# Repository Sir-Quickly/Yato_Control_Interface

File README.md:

# Yato_Control_Interface
Interface Leiterplatte zur Fernsteuerung von  YATO (YG-04700)- und Hendi (3500 M)-Induktionsplatten 

Achtung: Im Betrieb und selbst im ausgeschalteten Zustand können auf der Leiterplatte potentiell gefährliche Spannungen anliegen, selbst nach dem Ziehen des Netzsteckers durch geladenen Kapzitäten.
Die Benutzung dieses Designs erfolgt auf eigenes Risiko und nur durch fachkundige Personen, die sich über die Gefahren und Risiken im Klaren sind.

Änderungen gegenüber V1.0
- Pulldown Widerstand für das On-Signal von der YATO Poti-Platine
- Pos. R4 korrigiert

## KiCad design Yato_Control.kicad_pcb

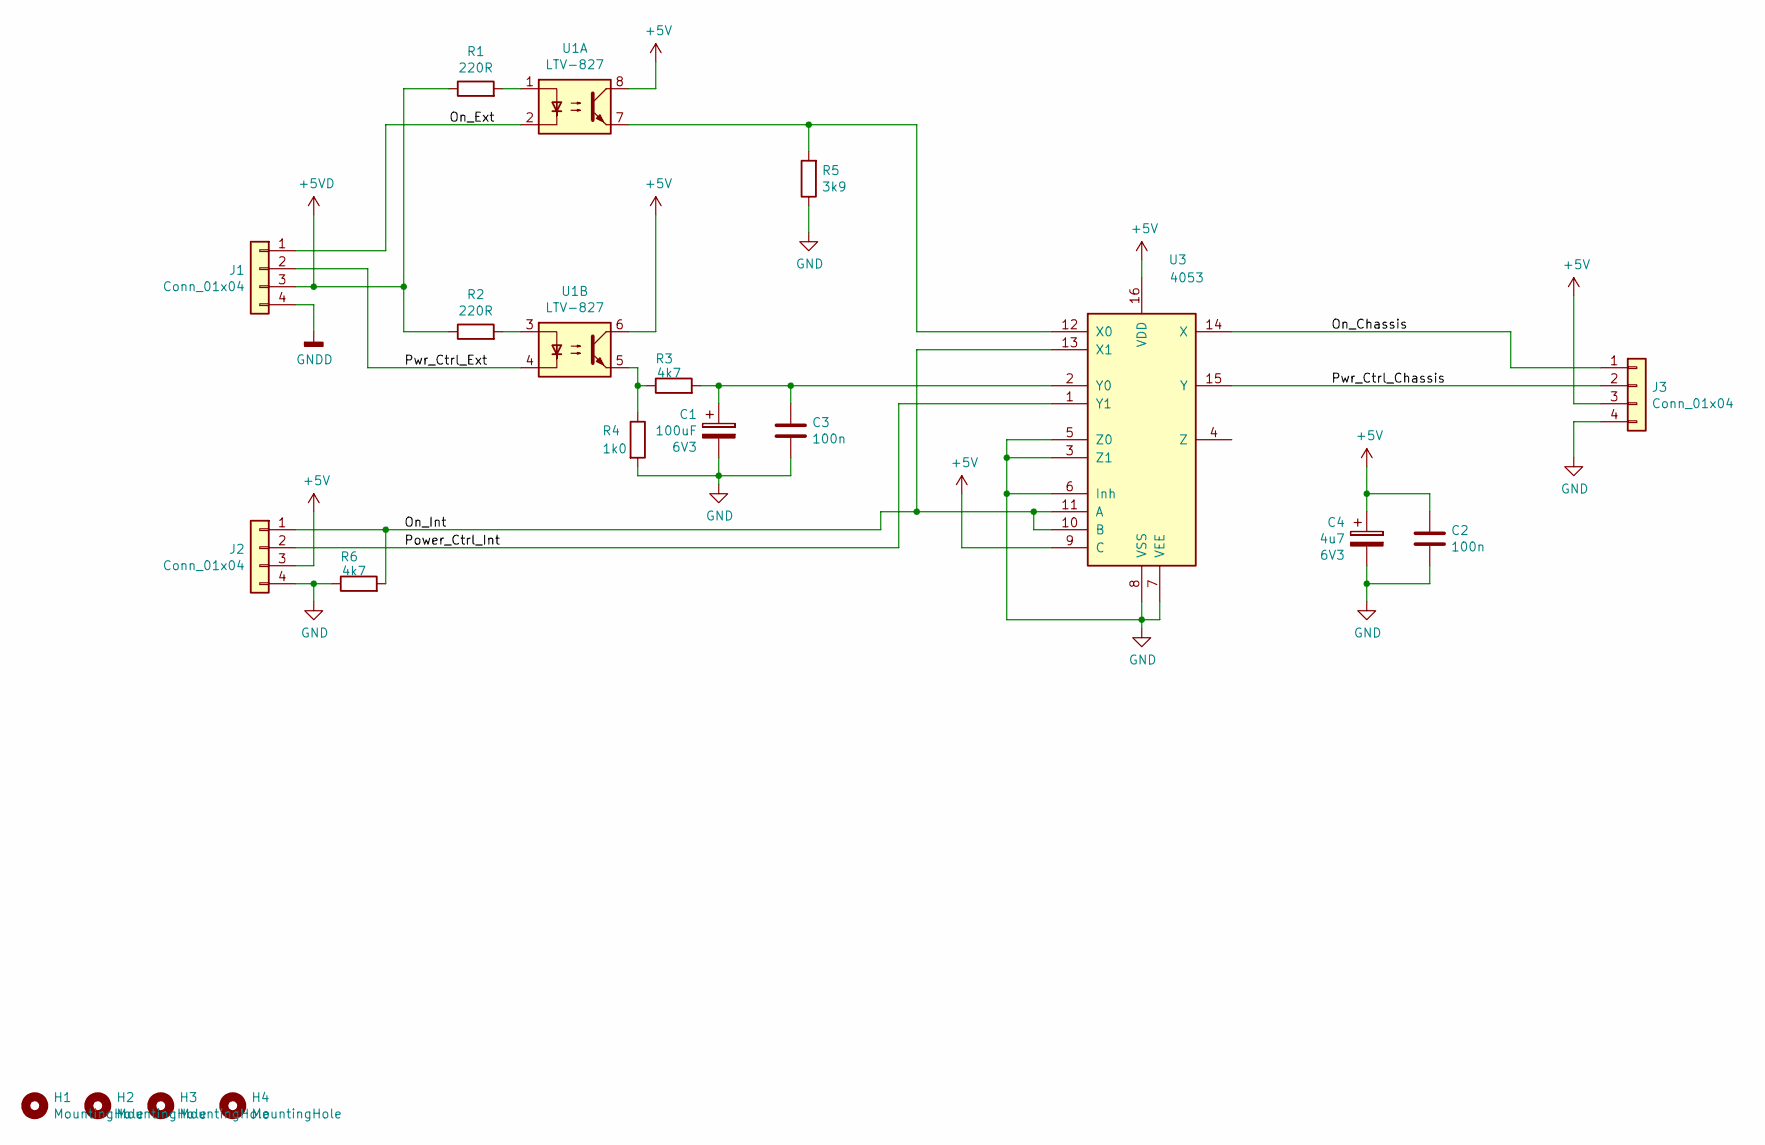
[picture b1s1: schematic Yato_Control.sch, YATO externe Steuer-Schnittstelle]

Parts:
C1: 100uF; CP_Radial_D10.0mm_P2.50mm_P5.00mm
C2, C3: 100n; C_Disc_D3.0mm_W1.6mm_P2.50mm
C4: 4u7; CP_Radial_D5.0mm_P2.50mm
H1, H2, H3, H4: MountingHole; MountingHole_4mm
J1, J2, J3: Conn_01x04; JST_XH_B04B-XH-A_1x04_P2.50mm_Vertical
R1, R2: 220R; R_Axial_DIN0207_L6.3mm_D2.5mm_P7.62mm_Horizontal
R3, R6: 4k7; R_Axial_DIN0207_L6.3mm_D2.5mm_P7.62mm_Horizontal
R4: 1k0; R_Axial_DIN0207_L6.3mm_D2.5mm_P7.62mm_Horizontal
R5: 3k9; R_Axial_DIN0207_L6.3mm_D2.5mm_P7.62mm_Horizontal
U1: LTV-827; DIP-8_W7.62mm
U3: 4053; DIP-16_W10.16mm

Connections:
+5V: C2.1, C4.1, J2.3, J3.3, U1.6, U1.8, U3.9 (C), U3.16 (VDD)
+5VD: J1.3, R1.1, R2.1
/On_Chassis: J3.1, U3.14 (X)
/On_Ext: J1.1, U1.2
/On_Int: J2.1, R6.2, U3.10 (B), U3.11 (A), U3.13 (X1)
/Power_Ctrl_Int: J2.2, U3.1 (Y1)
/Pwr_Ctrl_Chassis: J3.2, U3.15 (Y)
/Pwr_Ctrl_Ext: J1.2, U1.4
GND: C1.2, C2.2, C3.2, C4.2, J2.4, J3.4, R4.2, R5.1, R6.1, U3.3 (Z1), U3.5 (Z0), U3.6 (Inh), U3.7 (VEE), U3.8 (VSS)
GNDD: J1.4
unnamed: C1.1, C3.1, R3.2, U3.2 (Y0)
unnamed: R1.2, U1.1
unnamed: R2.2, U1.3
unnamed: R3.1, R4.1, U1.5
unnamed: R5.2, U1.7, U3.12 (X0)

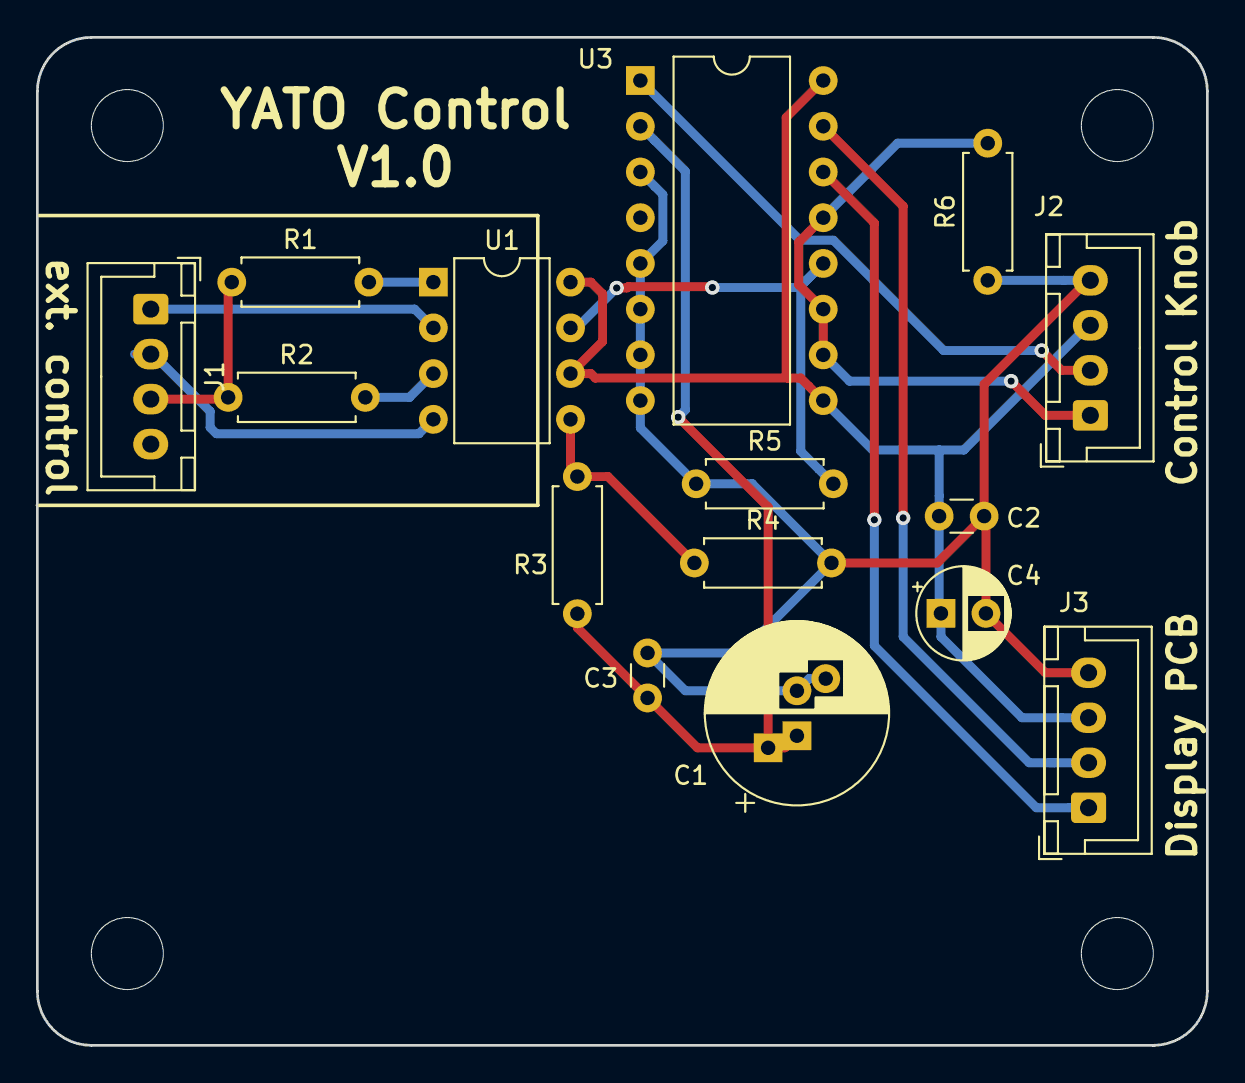
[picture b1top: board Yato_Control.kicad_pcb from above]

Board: 2 copper layers, 65.0 x 56.0 mm, 19 parts (0 on the bottom side), 14 nets.

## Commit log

2020-06-02 transferred project to Github inial commit
2020-06-05 initial layout done Signed-off-by: Sir Quickly <sir.quickly0@googlemail.com>
2020-07-25 - Pulldown Widerstand für das On-Signal von der YATO Poti-Platine - Pos. R4 korrigiert
